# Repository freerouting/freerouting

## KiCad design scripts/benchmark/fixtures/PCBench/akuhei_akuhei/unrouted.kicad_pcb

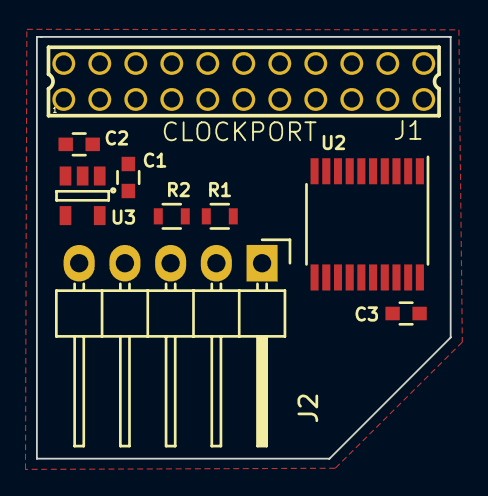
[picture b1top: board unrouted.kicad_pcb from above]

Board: 2 copper layers, 23.0 x 23.4 mm, 9 parts (0 on the bottom side), 20 nets, no tracks yet.

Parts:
C1: 1uF; C_0603
C2: 0.1uF; C_0603
C3: 100nF; C_0603
J1: CLOCKPORT; 87758-2216
J2: I2C; Pin_Header_Angled_1x05
R1, R2: 4.7k; R_0603
U2: PCA9564; TSSOP-20_4.4x6.5mm_Pitch0.65mm
U3: TLV70233DBV; SOT-23-5

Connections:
+3V3: C1.1, C3.1, J2.3, R1.2, R2.2, U2.20, U3.5
+5V: C2.1, J1.2, U3.1, U3.3
/A1: J1.12, U2.14
/A2: J1.11, U2.15
/D0: J1.20, U2.1
/D1: J1.19, U2.2
/D2: J1.18, U2.3
/D3: J1.17, U2.4
/D4: J1.16, U2.5
/D5: J1.15, U2.6
/D6: J1.14, U2.7
/D7: J1.13, U2.8
CP_CS: J1.4, U2.13
CP_INT: J1.3, U2.16
CP_IORD: J1.7, U2.12
CP_IOWR: J1.8, U2.11
CP_RESET: J1.22, U2.17
GND: C1.2, C2.2, C3.2, J1.1, J1.21, J2.1, J2.5, U2.10, U3.2
SCL: J2.2, R1.1, U2.18
SDA: J2.4, R2.1, U2.19

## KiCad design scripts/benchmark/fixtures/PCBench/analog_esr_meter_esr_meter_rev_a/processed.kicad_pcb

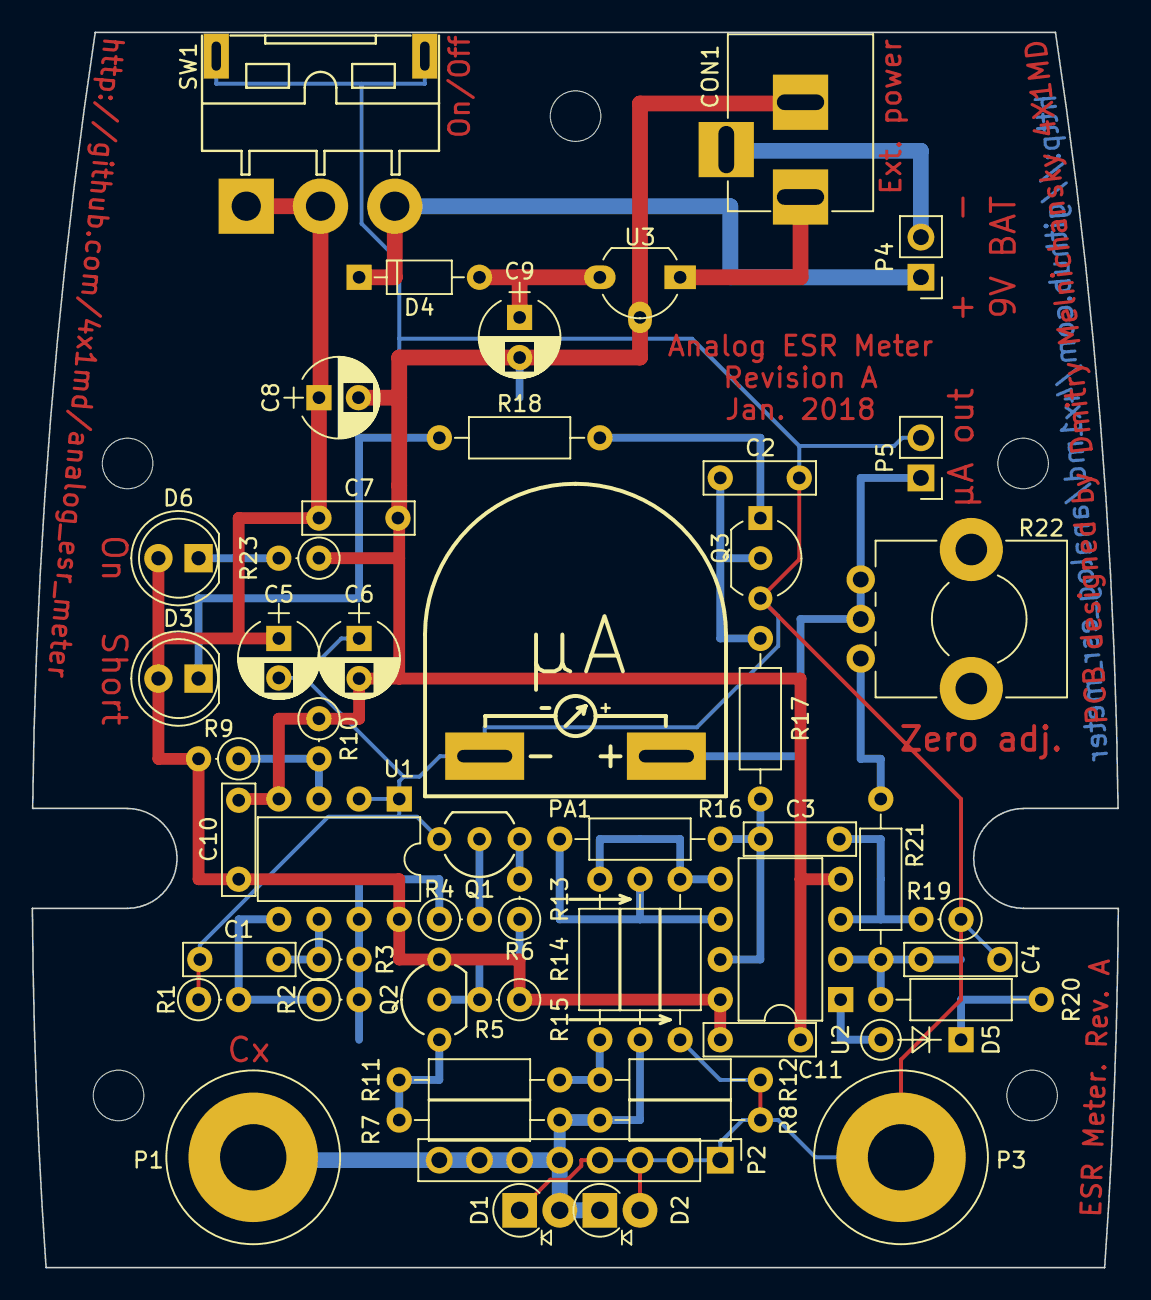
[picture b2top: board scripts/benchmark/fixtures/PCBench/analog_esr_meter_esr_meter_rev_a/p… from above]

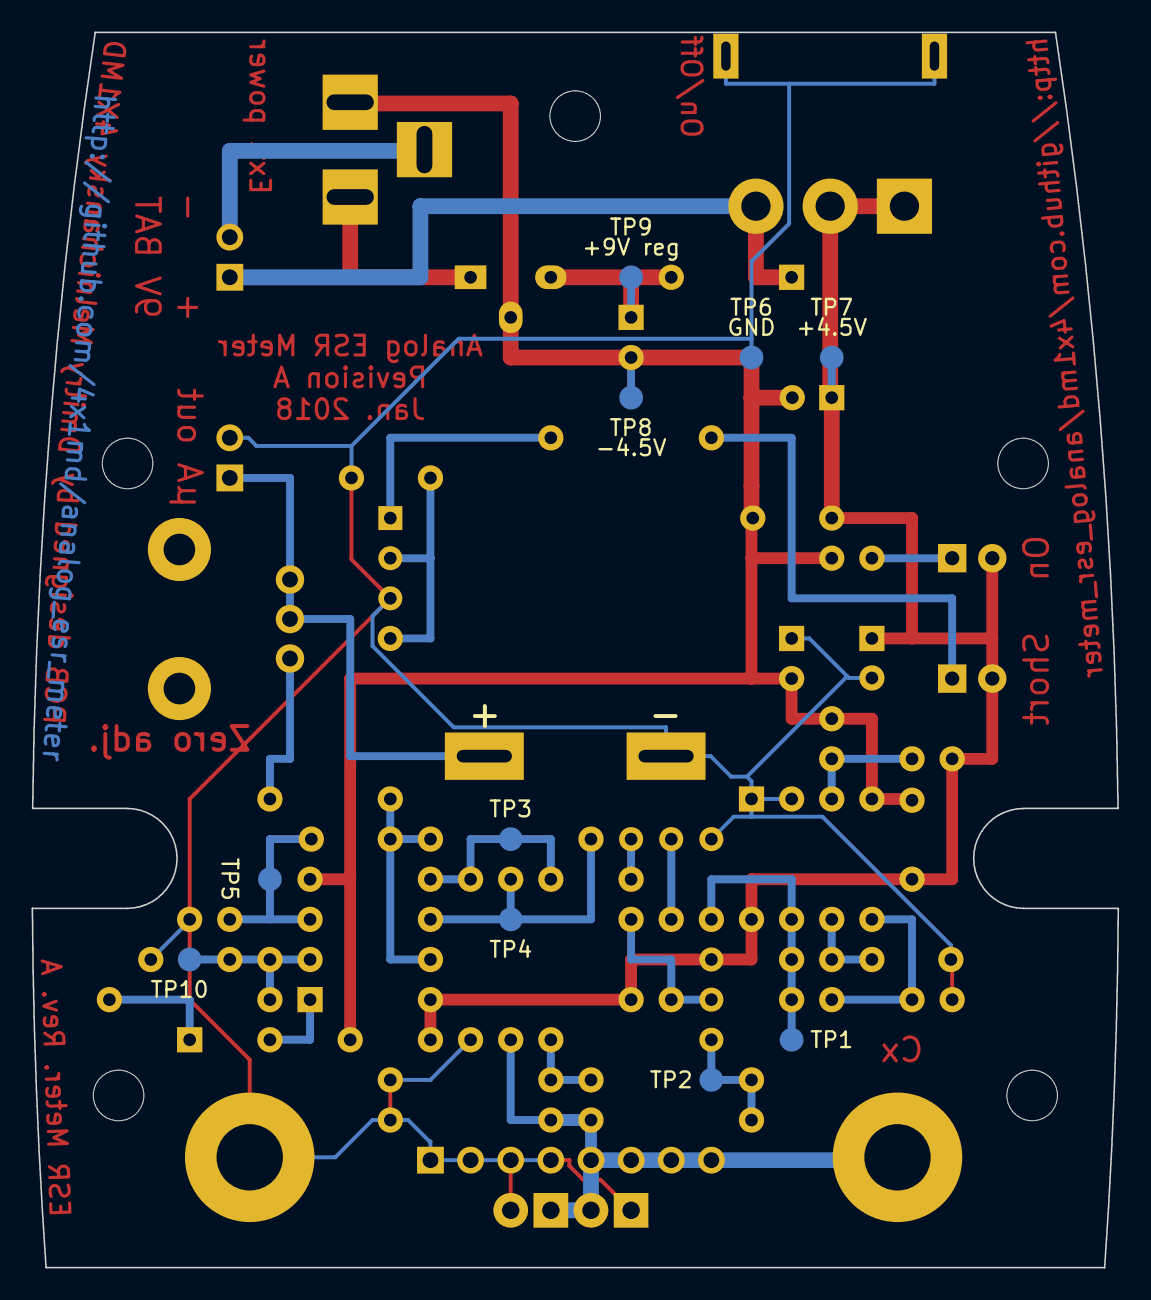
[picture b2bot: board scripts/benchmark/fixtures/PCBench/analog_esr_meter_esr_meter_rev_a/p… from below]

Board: 2 copper layers, 68.7 x 78.2 mm, 70 parts (10 on the bottom side), 30 nets.

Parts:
C1: 1nF; C_Rect_L7.0mm_W2.0mm_P5.00mm
C2, C4: 1uF; C_Rect_L7.0mm_W2.0mm_P5.00mm
C3, C7, C10, C11: 0.1uF; C_Rect_L7.0mm_W2.0mm_P5.00mm
C5, C6: 1uF; CP_Radial_D5.0mm_P2.50mm
C8: 22uF; CP_Radial_D5.0mm_P2.50mm
C9: 10uF; CP_Radial_D5.0mm_P2.50mm
CON1: External power; BARREL_JACK_PCB_EDGE
D1, D2: 1N4001; D_DO-41_SOD81_P2.54mm_Vertical_AnodeUp
D3: Red; LED_D5.0mm
D4: BAT60; D_DO-35_SOD27_P7.62mm_Horizontal
D5: 1N4148; D_DO-35_SOD27_P5.08mm_Vertical_KathodeUp
D6: Green; LED_D5.0mm
MH1, MH2, MH3, MH4, MH5: 3.2mm_M3_DIN965; MountingHole_3.2mm_M3_DIN965
MH**: 1.5mmx3.2mm_hole_for_wires
P1: Cx+; Banana_Jack_1Pin
P2: Cx; Socket_Strip_Straight_1x08_Pitch2.54mm
P3: Cx-; Banana_Jack_1Pin
P4: 9V battery; Pin_Header_Straight_1x02_Pitch2.54mm
P5: uA connector; Pin_Header_Straight_1x02_Pitch2.54mm
PA1: 50-250uA; Microampermeter
Q1, Q3: BC547; TO-92_Inline_Wide
Q2: BC557; TO-92_Inline_Wide
R1: 1.5K; R_Axial_DIN0207_L6.3mm_D2.5mm_P2.54mm_Vertical
R2, R3, R9, R10: 10K; R_Axial_DIN0207_L6.3mm_D2.5mm_P2.54mm_Vertical
R4: 68K; R_Axial_DIN0207_L6.3mm_D2.5mm_P2.54mm_Vertical
R5: 4.7K; R_Axial_DIN0207_L6.3mm_D2.5mm_P2.54mm_Vertical
R6: 12K; R_Axial_DIN0207_L6.3mm_D2.5mm_P2.54mm_Vertical
R7, R11, R13, R14, R21: 1K; R_Axial_DIN0207_L6.3mm_D2.5mm_P10.16mm_Horizontal
R8, R12: 22; R_Axial_DIN0207_L6.3mm_D2.5mm_P10.16mm_Horizontal
R15, R16: 47K; R_Axial_DIN0207_L6.3mm_D2.5mm_P10.16mm_Horizontal
R17: 15K; R_Axial_DIN0207_L6.3mm_D2.5mm_P10.16mm_Horizontal
R18: 470; R_Axial_DIN0207_L6.3mm_D2.5mm_P10.16mm_Horizontal
R19: 47K; R_Axial_DIN0207_L6.3mm_D2.5mm_P2.54mm_Vertical
R20: 47; R_Axial_DIN0207_L6.3mm_D2.5mm_P10.16mm_Horizontal
R22: 10K; Potentiometer_Alps_RK09K_Horizontal
R23: 470; R_Axial_DIN0207_L6.3mm_D2.5mm_P2.54mm_Vertical
SW1: On/Off; Switch_Slide_SPDT_THT_5MS1S102AM6QES
TP1: Osc. out; Measurement_Point_Round-SMD-Pad_Small
TP2: Bridge; Measurement_Point_Round-SMD-Pad_Small
TP3: Amp. (+); Measurement_Point_Round-SMD-Pad_Small
TP4: Amp (-); Measurement_Point_Round-SMD-Pad_Small
TP5: Amp. out; Measurement_Point_Round-SMD-Pad_Small
TP6: GND; Measurement_Point_Round-SMD-Pad_Small
TP7: +4.5V; Measurement_Point_Round-SMD-Pad_Small
TP8: -4.5V; Measurement_Point_Round-SMD-Pad_Small
TP9: +9V reg; Measurement_Point_Round-SMD-Pad_Small
TP10: Vout; Measurement_Point_Round-SMD-Pad_Small
U1, U2: TL082; DIP-8_W7.62mm
U3: LM7809CT; TO-92_Molded_Wide_Oval

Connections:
/+4.5V: C5.1, C7.1, C8.1, C10.1, C11.1, D3.2, D6.2, Q2.3, R5.1, R9.2, SW1.1, SW1.2, TP7.1, U1.8, U2.8
/+9V: D4.1, P4.1, SW1.3
/+9V_REG: C9.1, D4.2, TP9.1, U3.3
/-4.5V: C6.2, C7.2, C8.2, C9.2, C10.2, C11.2, CON1.2, R10.1, R23.1, TP8.1, U1.4, U2.4, U3.2
/CX: D1.2, D2.1, P1.1, P2.5, P2.6, P2.7, P2.8, R7.1, R8.1, R13.1
/EXT_VIN: CON1.1, U3.1
GNDREF: C1.2, C2.2, C4.2, C5.2, C6.1, D1.1, D2.2, P2.1, P2.2, P2.3, P2.4, P3.1, P5.2, PA1.2, Q1.3, Q3.3, R1.1, R8.2, R12.2, R15.1, R19.1, SW1.4, TP6.1, U1.1, U1.2
unnamed: C1.1, R3.1, U1.6
unnamed: C2.1, Q3.2, R17.1
unnamed: C3.1, R16.2, R17.2, U2.7
unnamed: C3.2, R19.2, TP5.1, U2.3
unnamed: C4.1, R20.1, R21.2, TP10.1, U2.2
unnamed: CON1.3, P4.2
unnamed: D3.1, R18.2
unnamed: D5.1, R20.2
unnamed: D5.2, U2.1
unnamed: D6.1, R23.2
unnamed: P5.1, PA1.1, R22.2, R22.3
unnamed: Q1.1, R6.2
unnamed: Q1.2, R4.2
unnamed: Q2.1, R7.2, R11.2, TP2.1
unnamed: Q2.2, R5.2, R6.1
unnamed: Q3.1, R18.1
unnamed: R1.2, R2.1, U1.5
unnamed: R2.2, R3.2, R4.1, TP1.1, U1.7
unnamed: R9.1, R10.2, U1.3
unnamed: R11.1, R12.1, R14.1
unnamed: R13.2, R16.1, TP4.1, U2.6
unnamed: R14.2, R15.2, TP3.1, U2.5
unnamed: R21.1, R22.1

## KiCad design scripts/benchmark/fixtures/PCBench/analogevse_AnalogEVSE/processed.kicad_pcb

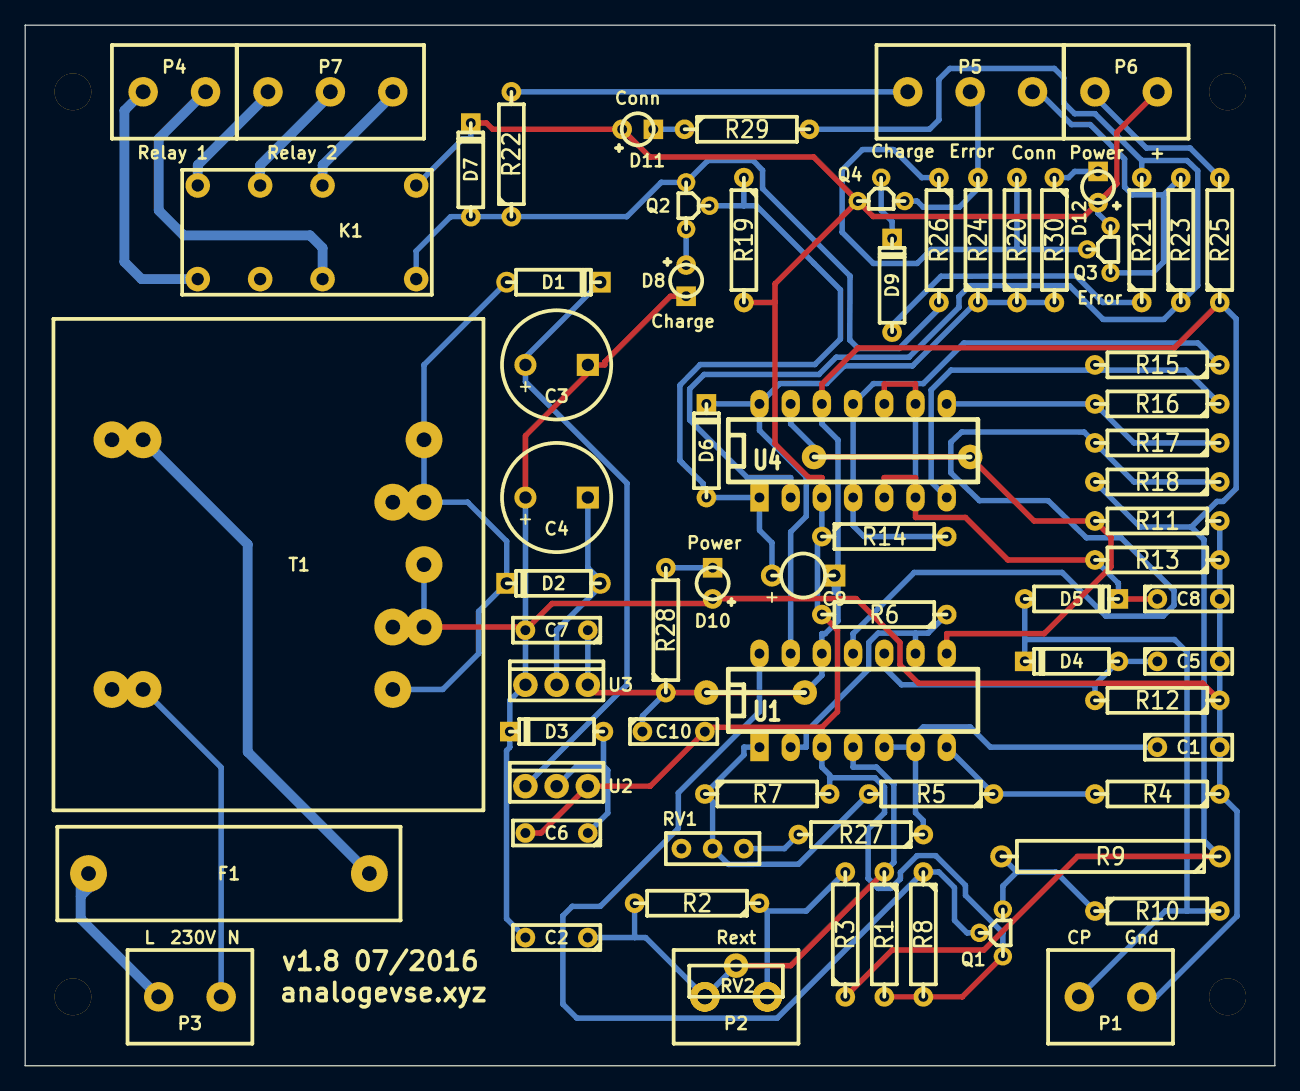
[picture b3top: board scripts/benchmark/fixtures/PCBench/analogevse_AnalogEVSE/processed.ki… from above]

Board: 2 copper layers, 101.7 x 84.7 mm, 80 parts (0 on the bottom side), 47 nets.

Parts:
C1: 5n6; C2
C2, C5, C6, C8: 100n; C2
C3, C4: 220u/25V; C5
C7: 220n; C2
C9: 4u7/16V; C6
C10: 150n; C2
D1, D2: 1N4002; D3-big
D3, D4, D5, D6, D7: 1N4148; D3
D8: Charging; LED-3
D9: SD101C; D3
D10: Power; LED-3
D11: Conn; LED-3
D12: Error; LED-3
F1: 100mA; Fuse-RM9
K1: Relay
Noname_1, Noname_2, Noname_3, Noname_8: WireBridgePad; DrillPad-3mm
Noname_4, Noname_5, Noname_6, Noname_7: WireBridgePad
P1: Pilot; Term-2pin
P2: Rext; Term-2pin
P3: 230V; Term-2pin
P4: Relay 1; Term-2pin
P5: Status LEDs; Term-3pin
P6: Power; Term-2pin
P7: Relay 2; Term-3pin
Q1, Q2, Q4: BC337-40; TO92
Q3: BC557; TO92
R1, R16: 5k6; R4-LARGE_PADS
R2, R6, R7, R8, R11, R21: 10k; R4-LARGE_PADS
R3: 1k5; R4-LARGE_PADS
R4, R5, R20, R26: 100k; R4-LARGE_PADS
R9: 1k/1W; R8
R10, R18: 1k; R4-LARGE_PADS
R12, R13: 1M; R4-LARGE_PADS
R14, R23, R24, R25, R28, R29, R30: 4k7; R4-LARGE_PADS
R15: 3k3; R4-LARGE_PADS
R17: 15k; R4-LARGE_PADS
R19, R27: 47k; R4-LARGE_PADS
R22: 2k2; R4-LARGE_PADS
RV1: 100k; Trimpot
RV2: 10k; Trimpot3
T1: 12V/3VA; Printtrafo
U1, U4: LM2901; IC-DIP-14
U2: LM7812
U3: LM7912

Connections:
+12V: C6.2, C10.2, D7.2, D11.1, D12.1, K1.9, P6.1, Q1.3, Q3.1, Q4.3, R1.2, R6.2, R7.2, R8.2, R14.1, R19.2, U1.3, U2.VO, U4.3
-12V: C7.1, C9.2, C10.1, Noname_4.2, Noname_5.2, R3.1, R9.1, R18.2, R25.1, R28.1, U1.12, U3.VO, U4.12
GND: C1.2, C2.2, C3.2, C4.1, C5.2, C7.2, C8.2, D3.2, D8.2, D10.1, P1.2, R4.1, R11.1, R12.1, R13.1, T1.4, U3.GND
unnamed: C1.1, R27.1, U1.5, U1.6
unnamed: C2.1, P2.1, R1.1, R2.2, RV2.1, RV2.2, U1.4
unnamed: C3.1, D1.2, U2.VI
unnamed: C4.2, D2.1, U3.VI
unnamed: C5.1, D4.1, R12.2, U1.10
unnamed: C6.1, D3.1, U2.GND
unnamed: C8.1, D5.2, R13.2, U4.5, U4.6, U4.9, U4.10
unnamed: C9.1, D6.1, Q2.2, R19.1, U4.1
unnamed: D1.1, D2.2, T1.3
unnamed: D4.2, D5.1, P1.1, R10.2
unnamed: D6.2, R20.1, R24.1, R30.2, U1.13, U4.14
unnamed: D7.1, K1.8, Q2.3, R22.1, R26.2
unnamed: D8.1, Q2.1
unnamed: D9.1, R21.1
unnamed: D9.2, Q4.2
unnamed: D10.2, R28.2
unnamed: D11.2, R29.1
unnamed: D12.2, R30.1
unnamed: F1.1, P3.1
unnamed: F1.2, T1.2
unnamed: K1.1, P4.2
unnamed: K1.5, P4.1
unnamed: K1.12, P7.1
unnamed: K1.14, P7.2
unnamed: K1.16, P7.3
unnamed: P2.2, R2.1, R3.2, RV2.3
unnamed: P3.2, T1.1
unnamed: P5.1, R22.2
unnamed: P5.2, Q4.1, R24.2
unnamed: P5.3, Q3.3, R23.2
unnamed: P6.2, R25.2
unnamed: Q1.1, R9.2, R10.1
unnamed: Q1.2, R8.1, U1.14
unnamed: Q3.2, R20.2, R26.1
unnamed: R4.2, R5.1, U1.7
unnamed: R5.2, R7.1, RV1.2, U1.1
unnamed: R6.1, U1.2, U1.9
unnamed: Noname_6.2, Noname_7.2, R11.2, U1.8, U4.13
unnamed: R21.2, R23.1, R29.2, U4.2
unnamed: R27.2, RV1.3
Vcharge: R15.2, R16.1, U4.7
Vconn: R14.2, R15.1, U4.4, U4.11
Vmin: R16.2, R17.1, U4.8
Vneg: R17.2, R18.1, U1.11
